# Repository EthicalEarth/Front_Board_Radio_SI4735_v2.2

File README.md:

# Front_Board_Radio_SI4735_v2.2
Untested Front Board - Developing. The main board is Arduino Nano Every.

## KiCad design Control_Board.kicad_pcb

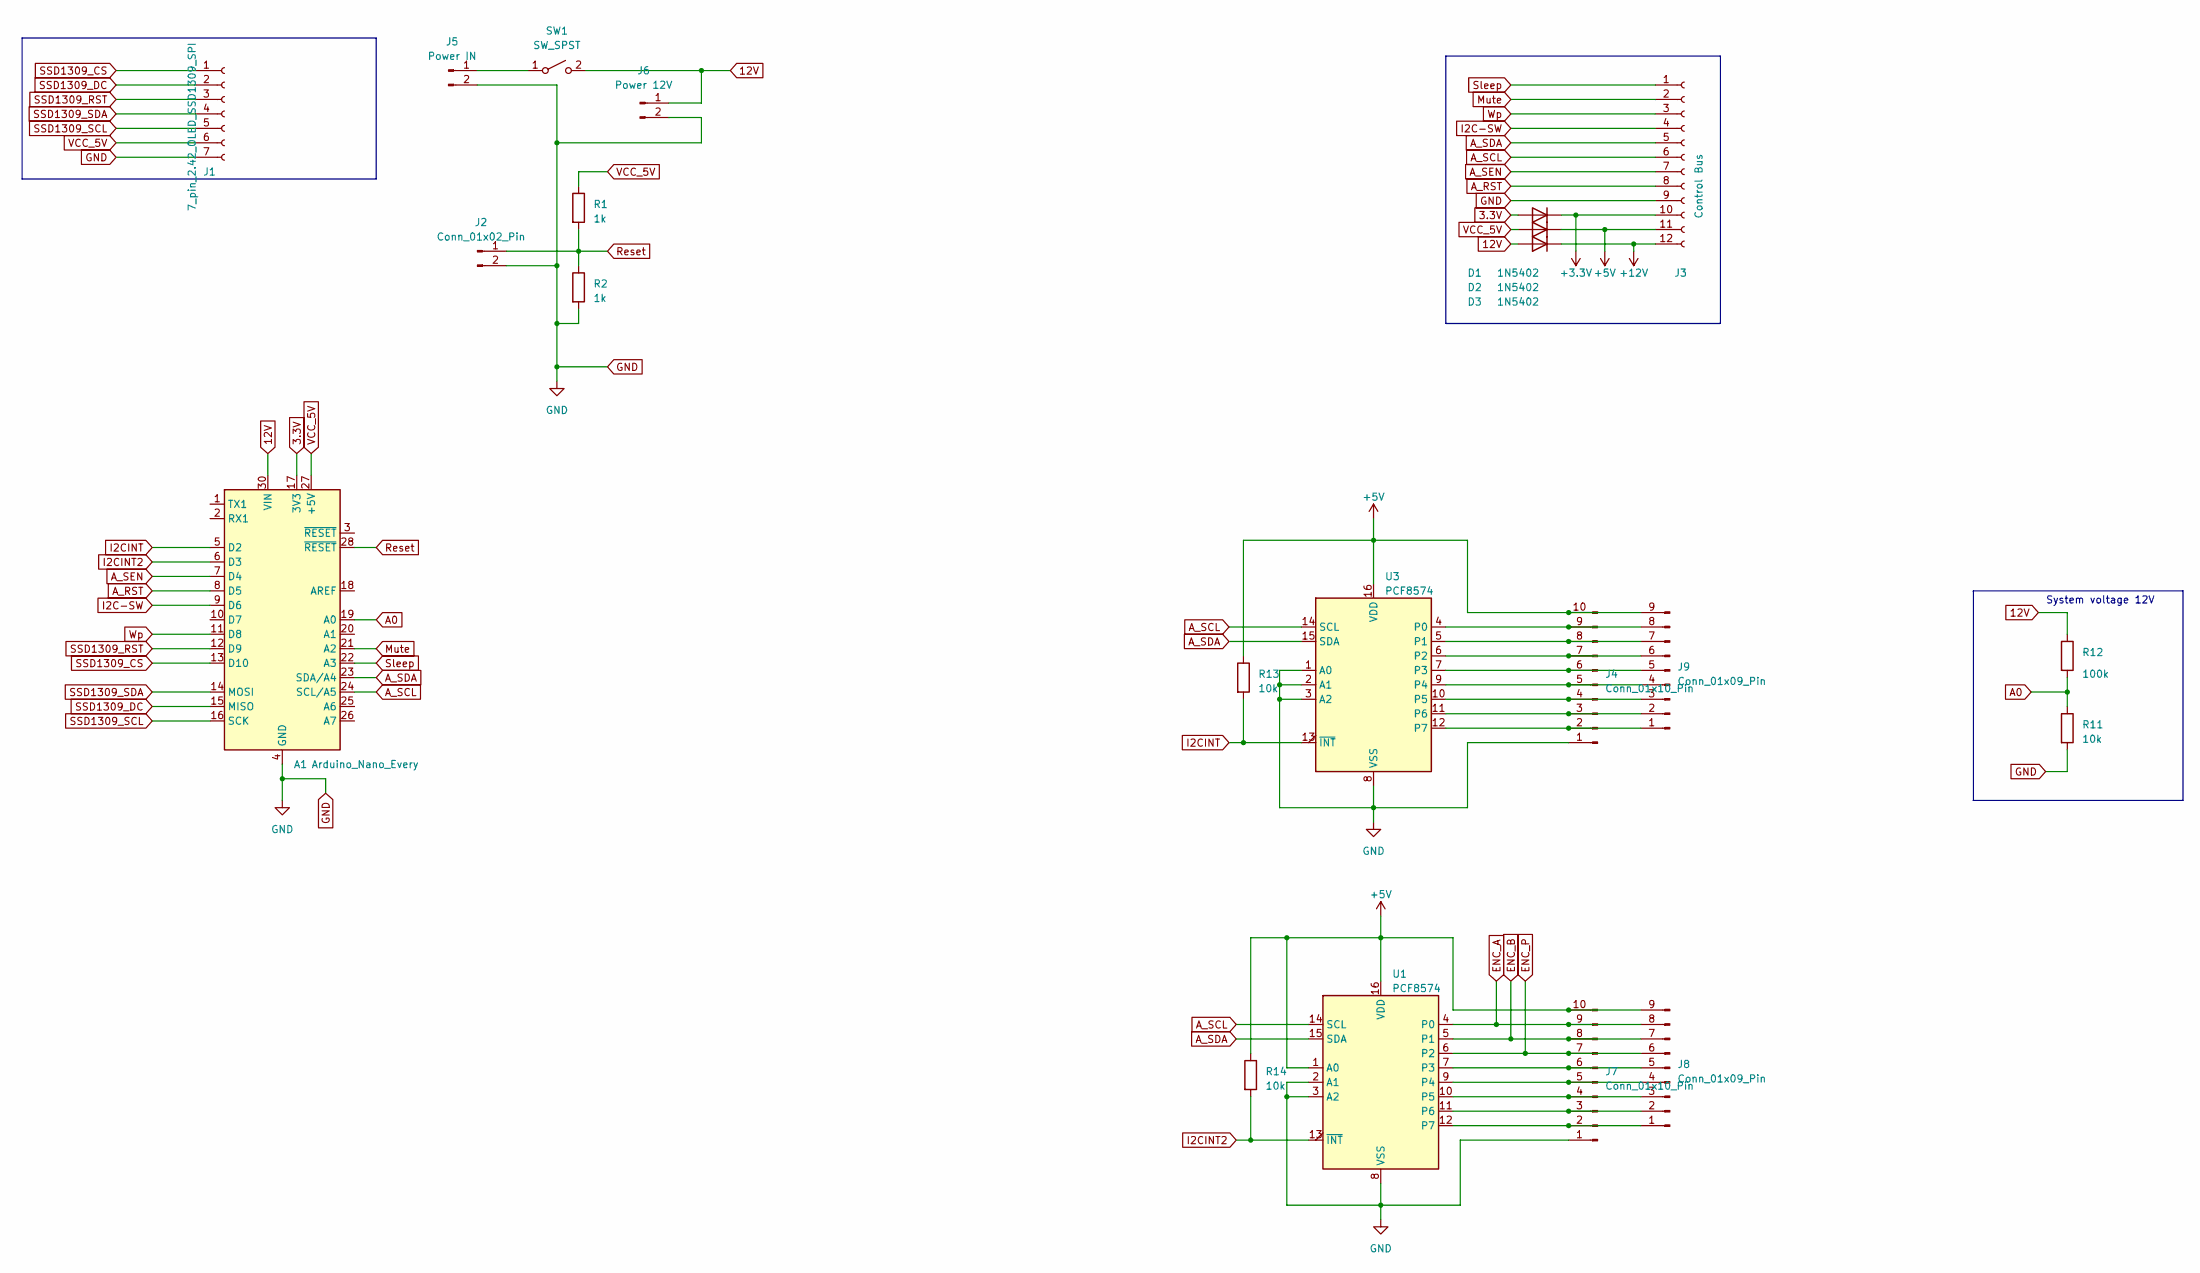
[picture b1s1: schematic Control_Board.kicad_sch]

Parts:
A1: Arduino_Nano_Every; Arduino_Nano
D1, D2, D3: 1N5402; D_1206_3216Metric
J1: 7_pin_2.42_OLED_SSD1309_SPI; PinSocket_1x07_P2.54mm_Vertical
J2: Conn_01x02_Pin; PinHeader_1x02_P1.27mm_Vertical
J3: Control Bus; PinSocket_1x12_P2.54mm_Vertical
J4, J7: Conn_01x10_Pin; PinSocket_1x10_P1.27mm_Vertical
J5: Power IN; PinSocket_1x02_P2.54mm_Vertical
J6: Power 12V; PinSocket_1x02_P2.54mm_Vertical
J8, J9: Conn_01x09_Pin; PinHeader_1x09_P2.54mm_Vertical
R1, R2: 1k; R_1206_3216Metric
R11, R13, R14: 10k; R_1206_3216Metric
R12: 100k; R_1206_3216Metric
SW1: SW_SPST; PinSocket_1x02_P2.54mm_Vertical
U1, U3: PCF8574; DIP-16_W7.62mm

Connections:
3.3V: A1.17 (3V3), D1.2 (A)
12V: A1.30 (VIN), D2.2 (A), J6.1, R12.1, SW1.2 (B)
+3V3: D1.1 (K), J3.10
+5V: D3.1 (K), J3.11, J4.10, J7.10, J8.9, J9.9, R13.1, R14.1, U1.1 (A0), U1.16 (VDD), U3.16 (VDD)
+12V: D2.1 (K), J3.12
A0: A1.19 (A0), R11.1, R12.2
A_RST: A1.8 (D5), J3.8
A_SCL: A1.24 (SCL/A5), J3.6, U1.14 (SCL), U3.14 (SCL)
A_SDA: A1.23 (SDA/A4), J3.5, U1.15 (SDA), U3.15 (SDA)
A_SEN: A1.7 (D4), J3.7
ENC_A: J7.9, J8.8, U1.4 (P0)
ENC_B: J7.8, J8.7, U1.5 (P1)
ENC_P: J7.7, J8.6, U1.6 (P2)
GND: A1.4 (GND), A1.29 (GND), J1.7, J2.2, J3.9, J4.1, J5.2, J6.2, J7.1, R2.2, R11.2, U1.2 (A1), U1.3 (A2), U1.8 (VSS), U3.1 (A0), U3.2 (A1), U3.3 (A2), U3.8 (VSS)
I2C-SW: A1.9 (D6), J3.4
I2CINT: A1.5 (D2), R13.2, U3.13 (~INT)
I2CINT2: A1.6 (D3), R14.2, U1.13 (~INT)
Mute: A1.21 (A2), J3.2
unnamed: J4.2, J9.1, U3.12 (P7)
unnamed: J4.3, J9.2, U3.11 (P6)
unnamed: J4.4, J9.3, U3.10 (P5)
unnamed: J4.5, J9.4, U3.9 (P4)
unnamed: J4.6, J9.5, U3.7 (P3)
unnamed: J4.7, J9.6, U3.6 (P2)
unnamed: J4.8, J9.7, U3.5 (P1)
unnamed: J4.9, J9.8, U3.4 (P0)
unnamed: J5.1, SW1.1 (A)
unnamed: J7.2, J8.1, U1.12 (P7)
unnamed: J7.3, J8.2, U1.11 (P6)
unnamed: J7.4, J8.3, U1.10 (P5)
unnamed: J7.5, J8.4, U1.9 (P4)
unnamed: J7.6, J8.5, U1.7 (P3)
Reset: A1.28 (~RESET), J2.1, R1.2, R2.1
SSD1309_CS: A1.13 (D10), J1.1
SSD1309_DC: A1.15 (MISO), J1.2
SSD1309_RST: A1.12 (D9), J1.3
SSD1309_SCL: A1.16 (SCK), J1.5
SSD1309_SDA: A1.14 (MOSI), J1.4
Sleep: A1.22 (A3), J3.1
VCC_5V: A1.27 (+5V), D3.2 (A), J1.6, R1.1
Wp: A1.11 (D8), J3.3

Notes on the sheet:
System voltage 12V

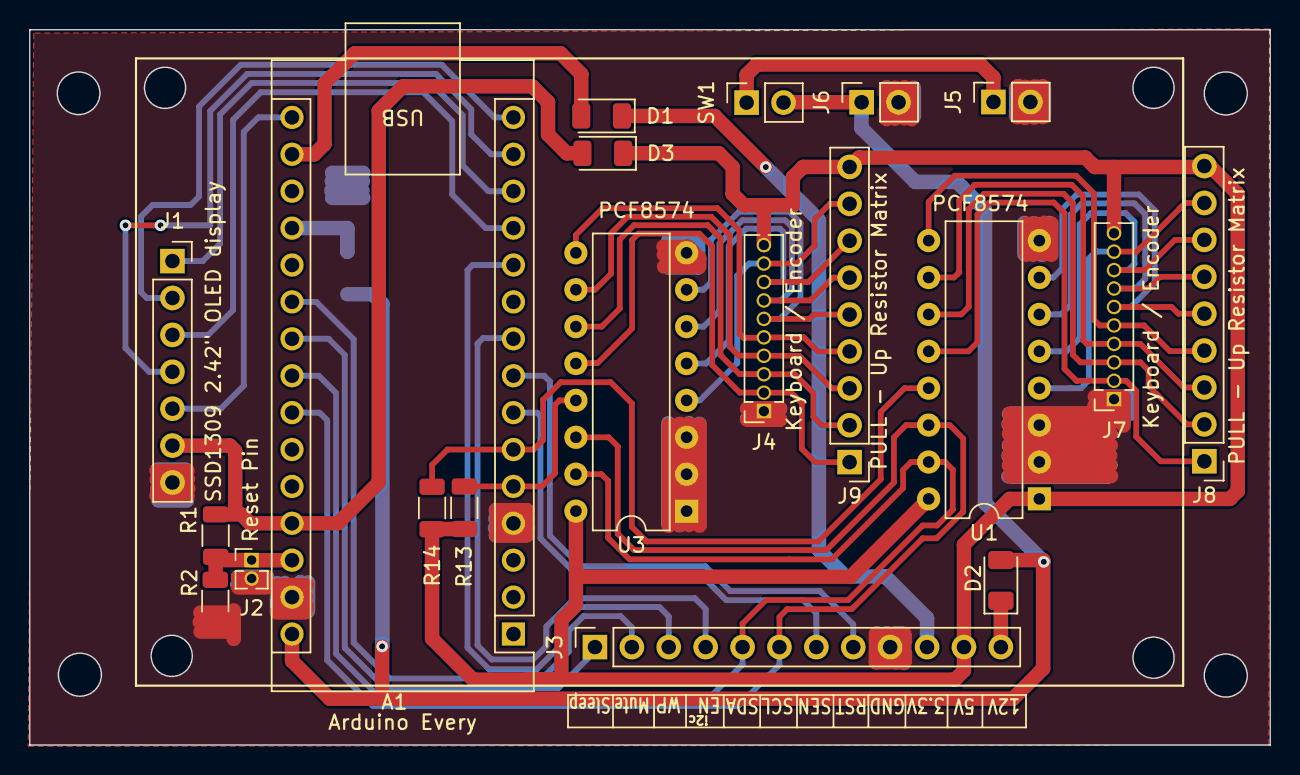
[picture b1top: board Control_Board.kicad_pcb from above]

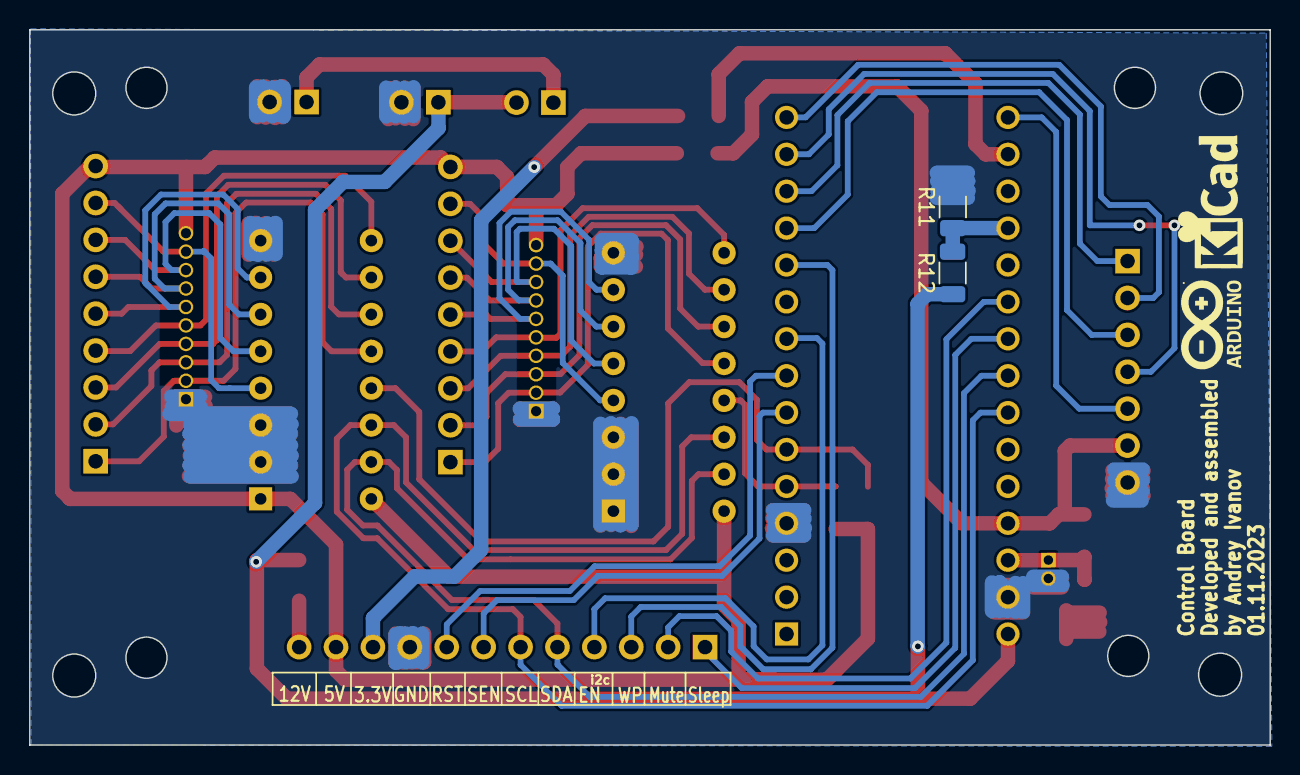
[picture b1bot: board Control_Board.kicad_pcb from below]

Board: 2 copper layers, 85.4 x 49.2 mm, 22 parts (2 on the bottom side), 41 nets.

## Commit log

2023-11-05 Init
